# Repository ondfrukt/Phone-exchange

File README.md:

# Phone Exchange - (Under development) # 

## Thanks to! ##

First of all, I want to thank my partner Amanda, who has been som patiant whit me - spending countless hours and weekends by my computer while I, for example, trying to figure out a way to capture pulses from rotary phones, or comforting during mental breakdowns when I was sodering without realizing I was using to low temperatur. If you are reading this - which you might not, since you're probebly so tierd of this project - I just want to say that i love you, and do that even more for standing out with me and my stupid phones.

I would also like to thank two GitHub members from whom I’ve drawn a lot of inspiration.

1. [GadgetReboot](https://github.com/GadgetReboot) with his YouTube videos and repositories about the KS0835F SLIC module and the MT8816 switch matrix, really made this project possible.

3. [Ktownsen](https://github.com/ktownsend-personal/) and his repository [RetroPhone](https://github.com/ktownsend-personal/RetroPhone) showed me that there is someone else out there who thinks an old wired phone network would be cool, and who shares the same passion for making vintage phones work just like they did back in the day. My call process modes and flows are heavily inspired by his work.

## Goal whit the project ##
The project aims to create a local wired phone network that supports both old rotary phones and newer DTMF tone-dialing phones. No intelligence or electronics will be built into the phones themselves; all logic and switching will be handled by the exchange unit. The network will follow a star topology, with two wires leading to each phone.

The goal is for the network to behave just like it did back in the day. Features such as ringing behavior, tones, and call logic will be implemented.

This is a learning project and my personal introduction to programming, Arduino, HTML, and electronics. It might eventually result in nothing more than a pile of electronic scrap and hundreds of non-functional lines of code—but it will definitely provide me with valuable knowledge and a steep learning curve.

### Typical behaviour for all call ###

A typical procedure of the system will be as shown below.
- A hook is lifted, the status of the line changes from "idle" to "ready" and a continuous tone can be heard in the phone hook.
- A phone number is dialed using pulse dialing or DTMF tones, and the digits are captured by the microcontroller.
- Ring pulses are generated to the dialed line and once the hook is picked up, the audio lines are connected between the two lines and the conversation can begin.
- Ones one of the connected phones puts it's handset into the crank, the audio connection between the lines breaks and the call ends.

## Hardware ##

| Component   | Description |
|-------------|-------------|
| ESP32-S3<br>  | - I have always appreciated the ESP family of microcontrollers. After first experimenting with Arduino modules such as the Arduino Uno and Arduino Uno WiFi, it quickly became clear that the ESP32 offered significantly more features at a lower cost. <br> - This module includes 8 MB of flash memory — an important improvement, since the 4 MB version ran out of space during earlier POC work. <br> - Like most ESP chips, it also provides both WiFi and Bluetooth, which are used here for the webserver and WiFi provisioning. The ESP32-C6 was initially considered due to its support for Matter and Zigbee. However, at the time it was not supported in PlatformIO, so the more common ESP32-S3 was selected for this project.
| MT8816<br>               | The MT8816 is a crosspoint swich matrix where you can connect one phone lines audio out to a certain lines audio in, and of course also in the opposite direction so a full audio connection is established more about how it works can be found [here](KiCad/ELEKTRONIK.md) (section 6)       | 
| MT8870<br>            | This circuit translates all tones from DTMF phones into digits.     |
| MCP23017            | GPIO expanders because the ESP32 do not have enough GPIO ports to control all devices                  |
| AD9833 module         | The AD9833 module, which I have three of in the exchange Is sending out tones into the swich matrix and then thuther to lines.               |
| KS0835F<br>          | This module may be the most important one on the breadboard. It handles the phone's behavior and converts it into signals that my ESP can process. It detects whether the phone's hook is on or off and can generate a ring frequency, which would otherwise be very complicated to produce.     |
| PCM5102<br>     | Audio files stored on the ESP are sent to this digital-to-analog converter to output audio messages to the lines when needed. The converter uses I²S communication with the ESP and outputs an analog representation of short, pre-stored audio clips. |
| TMUX4051<br>     | This audio multiplexer acts like a large switch, allowing the audio-out channel of each line to be selectively connected to the MT8870 DTMF detector. Only one channel at a time is connected to the DTMF decoder, and the system continuously sweeps through all lines that are in a state where tone detection is required.

In this way, it is possible to determine which line a tone originates from while using only a single DTMF detector.  |

## Webserver ##
I thought it would be good to have an interface where you could manage the phone system in some way, such as assigning a phone number to a specific line, activating/deactivating lines, changing the ring tone length, and adding some more features. During operation, access to the serial monitor will be limited, so having a way to easily tweak settings and access some debugging information would be useful.

The webserver can be reached at http://phoneexchange.local/ after the provisioning is completed

## MQTT ##
Having an MQTT function is also a goal so that the server can potentially interact with a smart home system such as Home Assistant, opening up the possibility to control home functions — just for fun!

## Line Statuses ##

To handle the logics in the exchange system, all lines has a current status whish triggers different logics in the system when they are changed.

### Status table ###
- Hook  :telephone_receiver: - If the phone hook is on or off due to the status
- Timer :stopwatch: - If the new status initiate a timer
- Audio :loud_sound: -  If a audio is played to the line due to the status (might not be implemented)
- Tone :postal_horn: - if a tone is played to the line due to the status

| Phone status  | Function                              | Hook     | Timer | Audio | Tone |
| ------------- | ------------------------------------- | -------- | ----- |-------|------| 
| idle          | Line is not in use                    | ✅ ON    | ❌    | ➖    | ❌   |
| ready         | Line is ready, waiting for inputs     | ⚪ OFF   | ✅    | ➖    | ✅   |
| puls_dialing  | Rotary dialing in progress            | ⚪ OFF   | ✅    | ➖    | ❌   |
| tone_dialing  | Touch-tone dialing in progress        | ⚪ OFF   | ✅    | ➖    | ❌   |
| busy          | Receiving busy signal                 | ⚪ OFF   | ✅    | ➖    | ✅   |
| fail          | Line failed to connect                | ⚪ OFF   | ✅    | ➖    | ✅   |
| ringing       | Line is ringing (outgoing call)       | ⚪ OFF   | ✅    | ➖    | ✅   |
| connected     | Call is active                        | ⚪ OFF   | ❌    | ➖    | ❌   |
| disconnected  | Call has ended, but line not yet idle | ⚪ OFF   | ✅    | ➖    | ❌   |
| timeout       | Line timed out                        | ⚪ OFF   | ✅    | ➖    | ✅   |
| abandoned     | Line was abandoned                    | ⚪ OFF   | ✅    | ➖    | ✅   |
| incoming      | Incoming call                         | ✅ ON    | ❌    | ➖    | ❌   |
| operator      | Connected to operator                 | ➖       | ❌    | ➖    | ❌   |

### Status flow chart ###
The flowchart below shows how the statuses change based on the behavior of the phone hooks or when status timers expire. This part is largely inspired by [GadgetReboot](https://github.com/GadgetReboot)
 and his repository “Retro Phone”. Many thanks to him!

## Challenges ##

- **SHK interference during ring signal generation**

The KS0835F SLIC's ring voltage (RM HIGH, FR toggling at 20 Hz) induces false SHK transitions, making it impossible to distinguish interference from a real pick-up. Simply ignoring SHK events during ringing suppresses the noise but also swallows genuine pick-ups — the interrupt is consumed and no new one fires during the pause, so the call never connects.

**Workaround in `SHKService`:** SHK events during `RingToggling` are still suppressed. When a line transitions from `RingToggling` to `RingPause`, the SHK pin is immediately force-polled. The debounce filter then confirms the true state: a real pick-up keeps SHK HIGH and the call connects; interference has already cleared and no change is registered. Maximum detection delay equals one ring-burst length (default 1 s).

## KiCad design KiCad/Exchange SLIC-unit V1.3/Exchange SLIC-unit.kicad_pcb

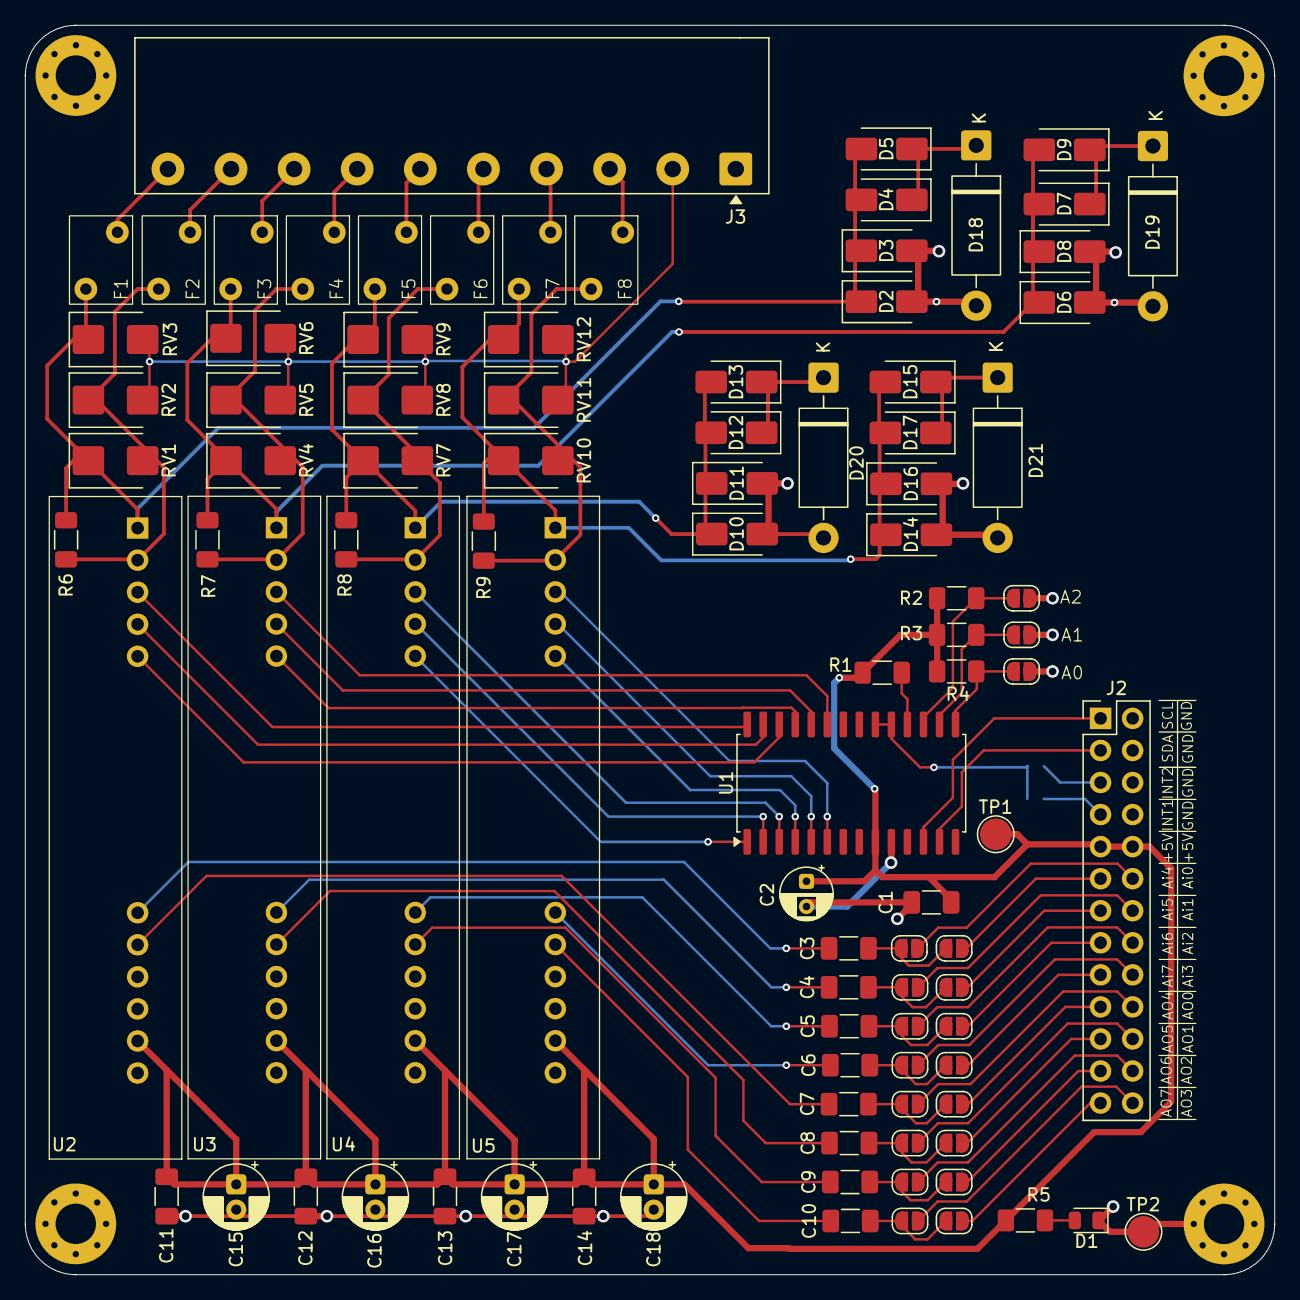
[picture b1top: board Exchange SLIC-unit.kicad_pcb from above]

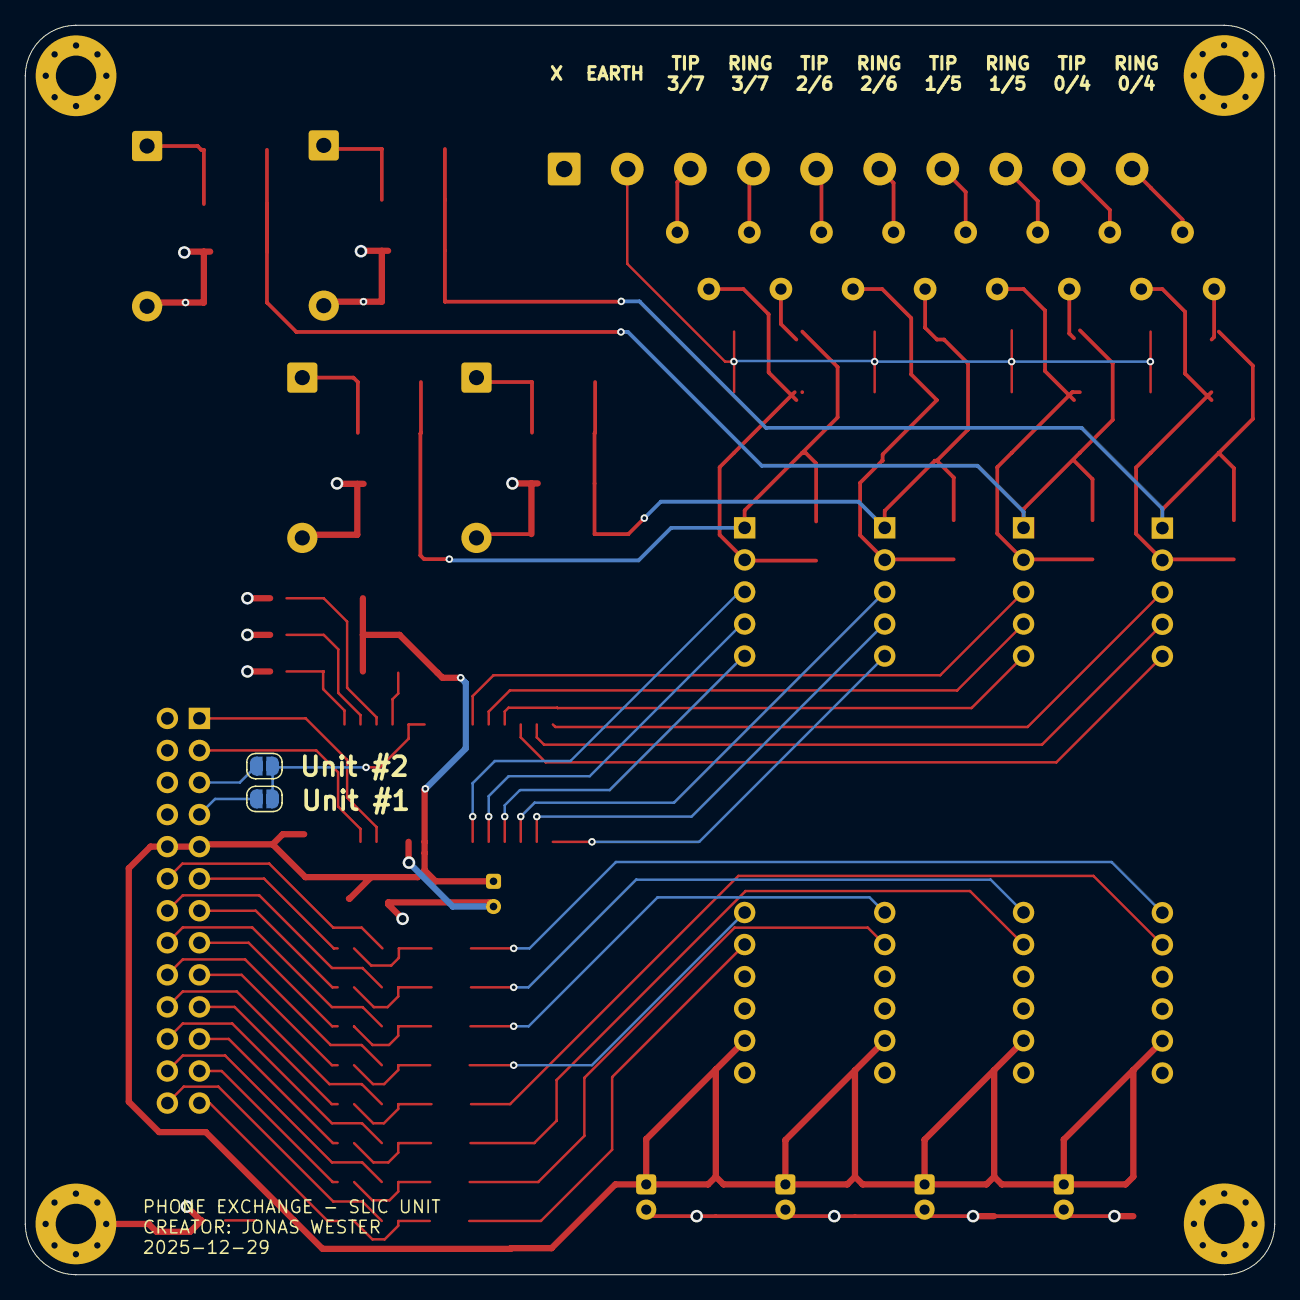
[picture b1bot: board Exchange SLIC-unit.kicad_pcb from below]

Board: 4 copper layers, 99.0 x 99.0 mm, 102 parts (2 on the bottom side), 77 nets.

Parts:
C1, C3, C4, C5, C6, C7, C8, C9, C10, C11, C12, C13, C14: 0.1uF; C_1206_3216Metric_Pad1.33x1.80mm_HandSolder
C2: 10uF; CP_Radial_D4.0mm_P2.00mm
C15, C16, C17, C18: 10uF; CP_Radial_D5.0mm_P2.00mm
D1: POWER LED; LED_0805_2012Metric
D2, D3, D4, D5, D6, D7, D8, D9, D10, D11, D12, D13, D14, D15, D16, D17: SM4004; D_SMA
D18, D19, D20, D21: P6KE51A; D_DO-15_P12.70mm_Horizontal
F1, F2, F3, F4, F5, F6, F7, F8: MF-R025; Fuse_Polyfuse_BK250_5.08mm_P0.8D1.8
H1, H2, H3, H4: MountingHole_Pad; MountingHole_3.2mm_M3_Pad_Via
J2: Conn_02x13_Odd_Even; PinHeader_2x13_P2.54mm_Vertical
J3: Screw_Terminal_01x10; TerminalBlock_Phoenix_MKDS-1,5-10_1x10_P5.00mm_Horizontal -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
JP1, JP2, JP3, JP4, JP5, JP6, JP7, JP8, JP9, JP10, JP11, JP12, JP13, JP14, JP15, JP16, JP17, JP18, JP19, JP20, JP21: SolderJumper_2_Open; SolderJumper-2_P1.3mm_Open_RoundedPad1.0x1.5mm
R1, R2, R3, R4: 10k; R_1206_3216Metric_Pad1.30x1.75mm_HandSolder
R5: 1k; R_1206_3216Metric_Pad1.30x1.75mm_HandSolder
R6, R7, R8, R9: 1M; R_1206_3216Metric_Pad1.30x1.75mm_HandSolder
RV1, RV2, RV3, RV4, RV5, RV6, RV7, RV8, RV9, RV10, RV11, RV12: Varistor; D_SMB
TP1, TP2: TestPoint; TestPoint_Pad_D2.5mm
U1: MCP23017; SOIC-28W_7.5x17.9mm_P1.27mm
U2, U3, U4, U5: KS0835F

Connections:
+5V: C1.2, C2.1, C11.1, C12.1, C13.1, C14.1, C15.1, C16.1, C17.1, C18.1, J2.9, J2.10, R1.1, R2.1, R3.1, R4.1, R5.1, TP1.1, U1.9 (VDD), U2.10 (+VDC), U3.10 (+VDC), U4.10 (+VDC), U5.10 (+VDC)
/Ain_0/4: C3.2, JP1.1 (A), JP9.2 (B)
/Ain_1/5: C4.2, JP2.1 (A), JP10.2 (B)
/Ain_2/6: C5.2, JP3.1 (A), JP11.2 (B)
/Ain_3/7: C6.2, JP4.1 (A), JP12.2 (B)
/Aout_0/4: C7.2, JP5.1 (A), JP13.2 (B)
/Aout_1/5: C8.2, JP6.1 (A), JP14.2 (B)
/Aout_2/6: C9.2, JP7.1 (A), JP15.2 (B)
/Aout_3/7: C10.2, JP8.1 (A), JP16.2 (B)
/FR_0/4: U1.28 (GPA7), U2.3 (F/R)
/FR_1/5: U1.23 (GPA2), U3.3 (F/R)
/FR_2/6: U1.3 (GPB2), U4.3 (F/R)
/FR_3/7: U1.6 (GPB5), U5.3 (F/R)
/MCP_SLIC_INT_1/2: JP17.1 (A), JP18.1 (A), U1.19 (INTB), U1.20 (INTA)
/RING_0/4: F1.2, J3.10
/RING_1/5: F3.2, J3.8
/RING_2/6: F5.2, J3.6
/RING_3/7: F7.2, J3.4
/RM_0/4: U1.27 (GPA6), U2.4 (RM)
/RM_1/5: U1.24 (GPA3), U3.4 (RM)
/RM_2/6: U1.2 (GPB1), U4.4 (RM)
/RM_3/7: U1.5 (GPB4), U5.4 (RM)
/SCL: J2.1, U1.12 (SCL)
/SDA: J2.3, U1.13 (SDA)
/SHK_0/4: U1.26 (GPA5), U2.5 (SHK)
/SHK_1/5: U1.25 (GPA4), U3.5 (SHK)
/SHK_2/6: U1.1 (GPB0), U4.5 (SHK)
/SHK_3/7: U1.4 (GPB3), U5.5 (SHK)
/TIP_0/4: F2.2, J3.9
/TIP_1/5: F4.2, J3.7
/TIP_2/6: F6.2, J3.5
/TIP_3/7: F8.2, J3.3
GND: C1.1, C2.2, C11.2, C12.2, C13.2, C14.2, C15.2, C16.2, C17.2, C18.2, D1.1 (K), D2.2 (A), D3.2 (A), D6.2 (A), D8.2 (A), D10.2 (A), D11.2 (A), D14.2 (A), D16.2 (A), D18.2, D19.2, D20.2, D21.2, H1.1, H2.1, H3.1, H4.1, J2.2, J2.4, J2.6, J2.8, JP19.2 (B), JP20.1 (A), JP21.1 (A), TP2.1, U1.10 (VSS), U2.9 (GND), U3.9 (GND), U4.9 (GND), U5.9 (GND)
GNDPWR: J3.2, RV2.2, RV3.2, RV5.2, RV6.2, RV8.2, RV9.2, RV11.2, RV12.2
unnamed: D1.2 (A), R5.2
unnamed: D2.1 (K), D3.1 (K), D4.2 (A), D5.2 (A), F1.1, R6.1, RV1.1, RV3.1, U2.1 (RING)
unnamed: D4.1 (K), D5.1 (K), D18.1
unnamed: D6.1 (K), D7.2 (A), D8.1 (K), D9.2 (A), F3.1, R7.1, RV4.1, RV6.1, U3.1 (RING)
unnamed: D7.1 (K), D9.1 (K), D19.1
unnamed: D10.1 (K), D11.1 (K), D12.2 (A), D13.2 (A), F5.1, R8.1, RV7.1, RV9.1, U4.1 (RING)
unnamed: D12.1 (K), D13.1 (K), D20.1
unnamed: D14.1 (K), D15.2 (A), D16.1 (K), D17.2 (A), F7.1, R9.1, RV10.1, RV12.1, U5.1 (RING)
unnamed: D15.1 (K), D17.1 (K), D21.1
unnamed: J2.5, JP18.2 (B)
unnamed: J2.7, JP17.2 (B)
unnamed: J2.11, JP9.1 (A)
unnamed: J2.12, JP1.2 (B)
unnamed: J2.13, JP10.1 (A)
unnamed: J2.14, JP2.2 (B)
unnamed: J2.15, JP11.1 (A)
unnamed: J2.16, JP3.2 (B)
unnamed: J2.17, JP12.1 (A)
unnamed: J2.18, JP4.2 (B)
unnamed: J2.19, JP13.1 (A)
unnamed: J2.20, JP5.2 (B)
unnamed: J2.21, JP14.1 (A)
unnamed: J2.22, JP6.2 (B)
unnamed: J2.23, JP15.1 (A)
unnamed: J2.24, JP7.2 (B)
unnamed: J2.25, JP16.1 (A)
unnamed: J2.26, JP8.2 (B)
unnamed: JP19.1 (A), R2.2, U1.17 (A2)
unnamed: JP20.2 (B), R3.2, U1.16 (A1)
unnamed: JP21.2 (B), R4.2, U1.15 (A0)
unnamed: R1.2, U1.18 (~RESET)
unnamed: C3.1, U2.6 (Audio_in)
unnamed: C7.1, U2.7 (Audio_out)
unnamed: F2.1, R6.2, RV1.2, RV2.1, U2.2 (TIP)
unnamed: C4.1, U3.6 (Audio_in)
unnamed: C8.1, U3.7 (Audio_out)
unnamed: F4.1, R7.2, RV4.2, RV5.1, U3.2 (TIP)
unnamed: C5.1, U4.6 (Audio_in)
unnamed: C9.1, U4.7 (Audio_out)
unnamed: F6.1, R8.2, RV7.2, RV8.1, U4.2 (TIP)
unnamed: C6.1, U5.6 (Audio_in)
unnamed: C10.1, U5.7 (Audio_out)
unnamed: F8.1, R9.2, RV10.2, RV11.1, U5.2 (TIP)

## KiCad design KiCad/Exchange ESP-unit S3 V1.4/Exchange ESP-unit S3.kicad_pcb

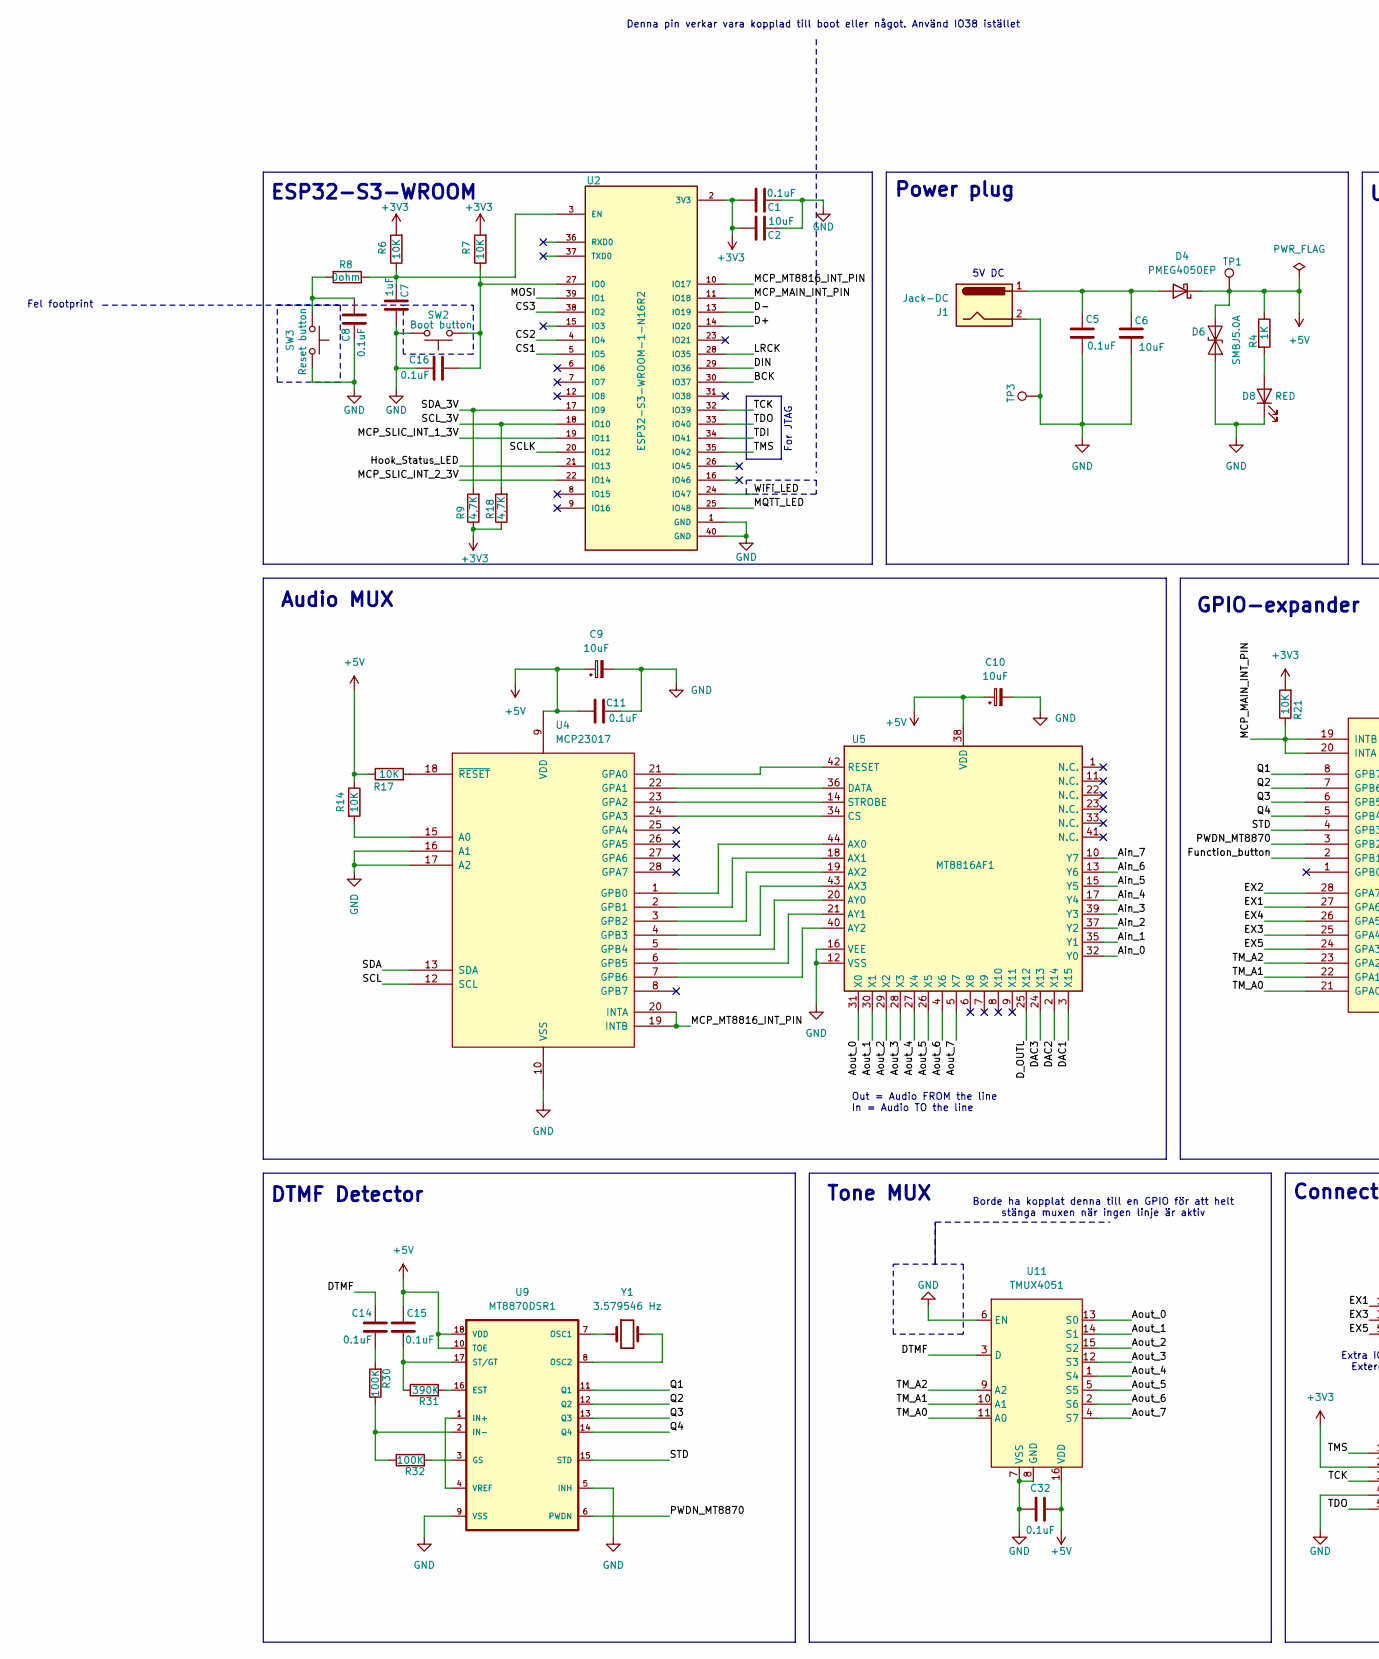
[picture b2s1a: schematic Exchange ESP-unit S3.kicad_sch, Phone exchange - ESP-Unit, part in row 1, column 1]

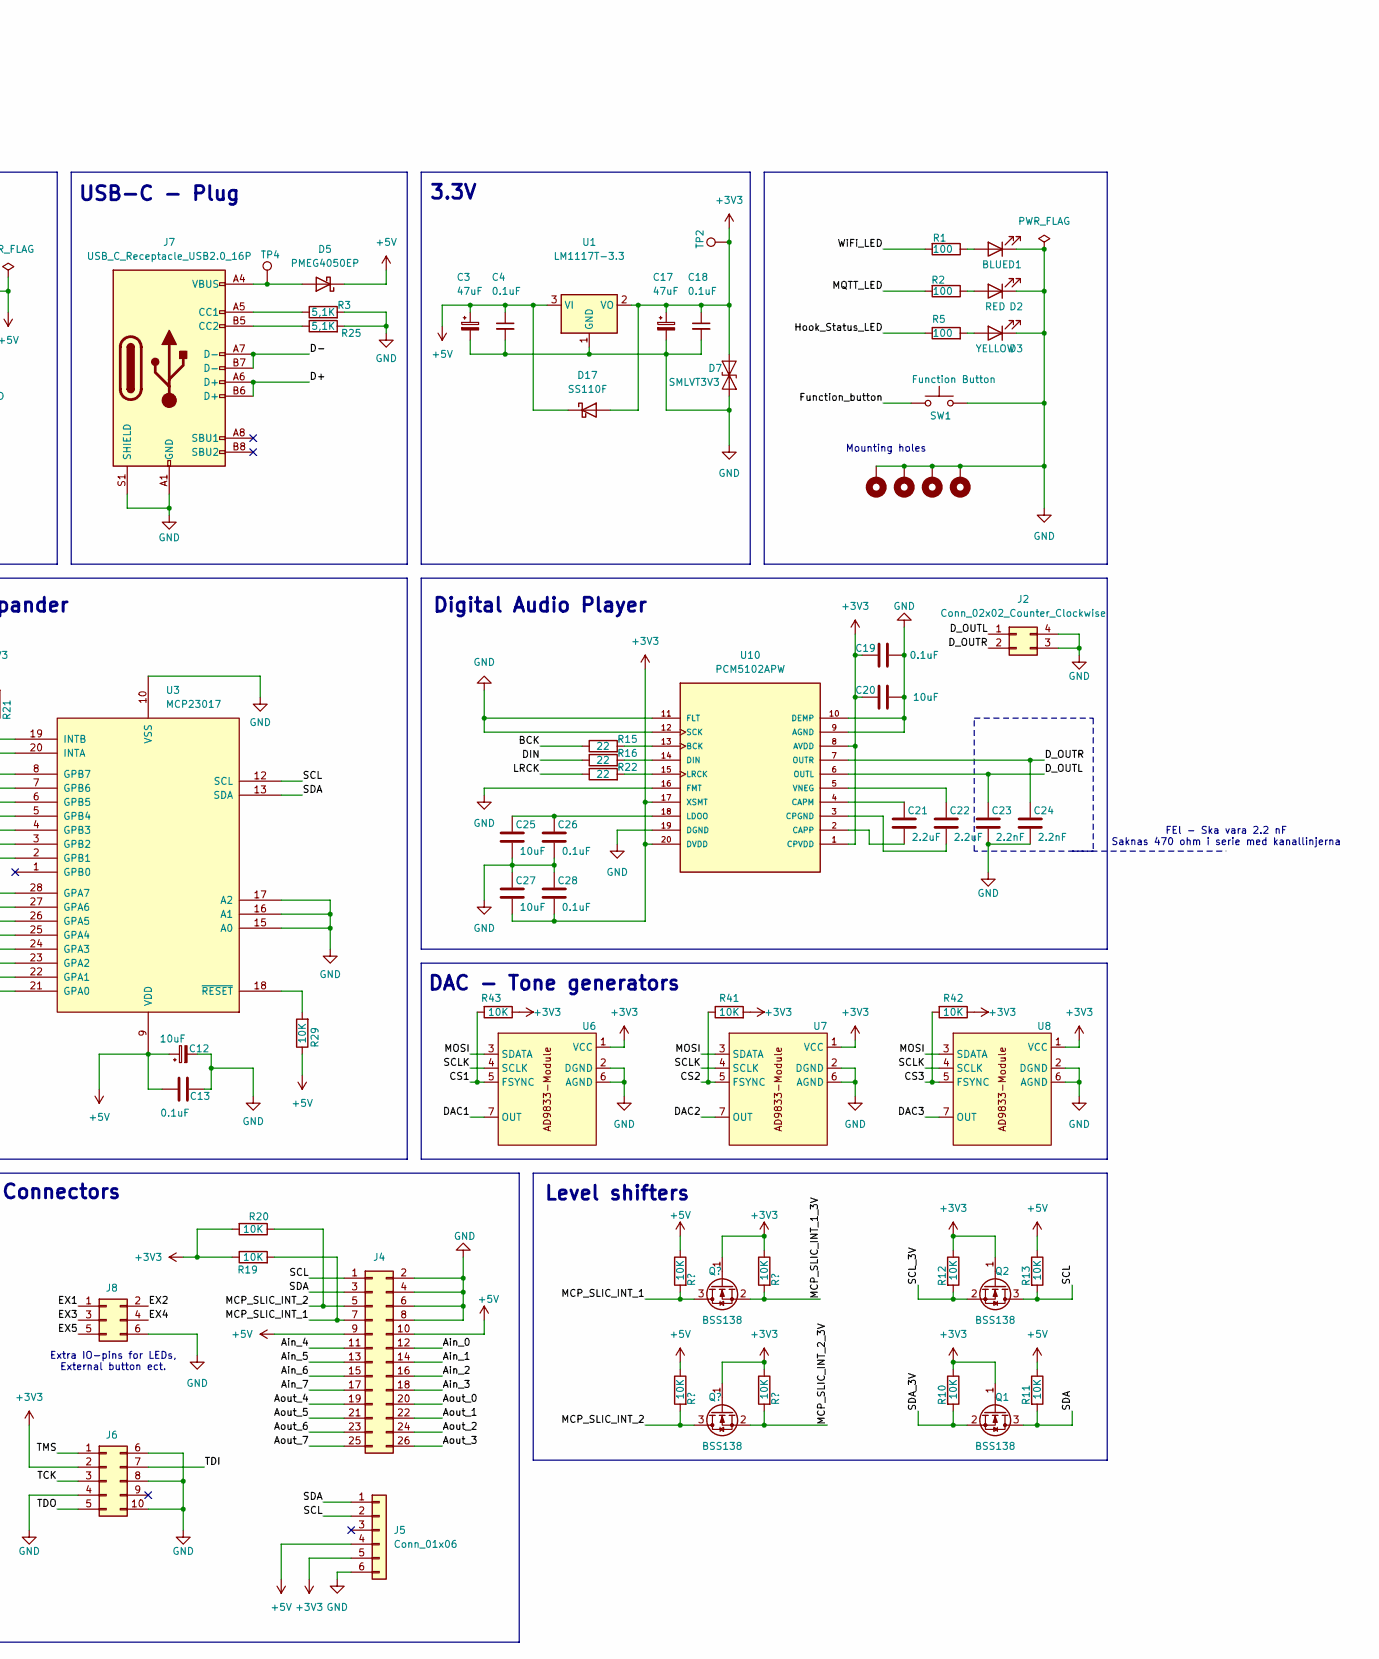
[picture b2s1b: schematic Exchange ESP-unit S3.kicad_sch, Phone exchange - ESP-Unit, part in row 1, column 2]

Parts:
C1, C4, C5, C8, C11, C13, C14, C15, C16, C18, C19, C26, C28, C32: 0.1uF; C_1206_3216Metric_Pad1.33x1.80mm_HandSolder
C2, C6, C20, C25, C27: 10uF; C_1206_3216Metric_Pad1.33x1.80mm_HandSolder
C3, C17: 47uF; CP_Radial_D4.0mm_P2.00mm
C7: 1uF; C_1206_3216Metric_Pad1.33x1.80mm_HandSolder
C9, C10, C12: 10uF; CP_Radial_D4.0mm_P2.00mm
C21, C22: 2.2uF; C_1206_3216Metric_Pad1.33x1.80mm_HandSolder
C23, C24: 2.2nF; C_1206_3216Metric_Pad1.33x1.80mm_HandSolder
D1: BLUE; LED_0805_2012Metric_Pad1.15x1.40mm_HandSolder
D2, D8: RED; LED_0805_2012Metric_Pad1.15x1.40mm_HandSolder
D3: YELLOW; LED_0805_2012Metric_Pad1.15x1.40mm_HandSolder
D4, D5: PMEG4050EP; D_SOD-128
D6: SMBJ5.0A; D_SMB
D7: SMLVT3V3; D_SMB_Handsoldering
D17: SS110F; D_SMA_Handsoldering
H1, H2, H3, H4: MountingHole_Pad; MountingHole_3.2mm_M3_Pad_Via
J1: Jack-DC; BarrelJack_Horizontal
J2: Conn_02x02_Counter_Clockwise; PinHeader_2x02_P2.54mm_Vertical
J4: Conn_02x13_Odd_Even; PinSocket_2x13_P2.54mm_Vertical
J5: Conn_01x06; PinHeader_1x06_P2.54mm_Vertical
J6: Conn_02x05_Top_Bottom; PinSocket_2x05_P2.54mm_Vertical
J7: USB_C_Receptacle_USB2.0_16P; USB_C_Receptacle_GCT_USB4105-xx-A_16P_TopMnt_Horizontal
J8: Conn_02x03_Odd_Even; PinHeader_2x03_P2.54mm_Vertical
Q1, Q2: BSS138; SOT-23
R1, R2, R5: 100; R_1206_3216Metric_Pad1.30x1.75mm_HandSolder
R3, R25: 5,1K; R_1206_3216Metric_Pad1.30x1.75mm_HandSolder
R4: 1K; R_1206_3216Metric_Pad1.30x1.75mm_HandSolder
R6, R7, R10, R11, R12, R13, R14, R17, R19, R20, R21, R29, R41, R42, R43: 10K; R_1206_3216Metric_Pad1.30x1.75mm_HandSolder
R8: 0ohm; R_1206_3216Metric_Pad1.30x1.75mm_HandSolder
R9, R18: 4,7K; R_1206_3216Metric_Pad1.30x1.75mm_HandSolder
R15, R16, R22: 22; R_1206_3216Metric_Pad1.30x1.75mm_HandSolder
R30, R32: 100K; R_1206_3216Metric_Pad1.30x1.75mm_HandSolder
R31: 390K; R_1206_3216Metric_Pad1.30x1.75mm_HandSolder
SW1: Function Button; SW_SPST_TL3305B
SW2: Boot button; SW_SPST_TL3305B
SW3: Reset button; SW_SPST_TL3305B
TP1, TP2, TP3, TP4: TestPoint; TestPoint_Pad_D2.0mm
U1: LM1117T-3.3; TO-220-3_Vertical
U2: ESP32-S3-WROOM-1-N16R2; XCVR_ESP32-S3-WROOM-1-N16; PARTREV v1.0
U3, U4: MCP23017; SOIC-28W_7.5x17.9mm_P1.27mm
U5: MT8816AF1; TQFP-44_10x10mm_P0.8mm
U6, U7, U8: AD9833-module; AD9833-Module
U9: MT8870DSR1; SOIC-18W_7.5x11.6mm_P1.27mm
U10: PCM5102APW; TSSOP-20_4.4x6.5mm_P0.65mm; PARTREV C
U11: TMUX4051; TSSOP-16_4.4x5mm_P0.65mm
Y1: 3.579546 Hz; Crystal_HC49-4H_Vertical

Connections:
+5V: C3.1, C4.1, C9.1, C10.1, C11.1, C12.1, C13.2, C15.1, C32.2, D4.1 (K), D5.1 (K), D6.1 (A1), D17.1 (K), J4.9, J4.10, J5.4, R4.1, R11.1, R13.1, R14.1, R17.1, R29.1, TP1.1, U1.3 (VI), U3.9 (VDD), U4.9 (VDD), U5.38 (VDD), U9.10 (TOE), U9.18 (VDD), U11.16 (VDD)
/Ain_0: J4.12, U5.32 (Y0)
/Ain_1: J4.14, U5.35 (Y1)
/Ain_2: J4.16, U5.37 (Y2)
/Ain_3: J4.18, U5.39 (Y3)
/Ain_4: J4.11, U5.17 (Y4)
/Ain_5: J4.13, U5.15 (Y5)
/Ain_6: J4.15, U5.13 (Y6)
/Ain_7: J4.17, U5.10 (Y7)
/Aout_0: J4.20, U5.31 (X0), U11.13 (S0)
/Aout_1: J4.22, U5.30 (X1), U11.14 (S1)
/Aout_2: J4.24, U5.29 (X2), U11.15 (S2)
/Aout_3: J4.26, U5.28 (X3), U11.12 (S3)
/Aout_4: J4.19, U5.27 (X4), U11.1 (S4)
/Aout_5: J4.21, U5.26 (X5), U11.5 (S5)
/Aout_6: J4.23, U5.4 (X6), U11.2 (S6)
/Aout_7: J4.25, U5.5 (X7), U11.4 (S7)
/BCK: R15.1, U2.30 (IO37)
/CS1: R43.2, U2.5 (IO5), U6.5 (FSYNC)
/CS2: R41.1, U2.4 (IO4), U7.5 (FSYNC)
/CS3: R42.2, U2.38 (IO2), U8.5 (FSYNC)
/D+: J7.A6 (D+), J7.B6 (D+), U2.14 (IO20)
/D-: J7.A7 (D-), J7.B7 (D-), U2.13 (IO19)
/DAC1: U5.3 (X15), U6.7 (OUT)
/DAC2: U5.2 (X14), U7.7 (OUT)
/DAC3: U5.24 (X13), U8.7 (OUT)
/DIN: R16.1, U2.29 (IO36)
/DTMF: C14.2, U11.3 (D)
/D_OUTL: C23.1, J2.1, U5.25 (X12), U10.6 (OUTL)
/D_OUTR: C24.1, J2.2, U10.7 (OUTR)
/EX1: J8.1, U3.27 (GPA6)
/EX2: J8.2, U3.28 (GPA7)
/EX3: J8.3, U3.25 (GPA4)
/EX4: J8.4, U3.26 (GPA5)
/EX5: J8.5, U3.24 (GPA3)
/Function_button: SW1.2, U3.2 (GPB1)
/Hook_Status_LED: R5.1, U2.21 (IO13)
/LRCK: R22.1, U2.28 (IO35)
/MCP_MAIN_INT_PIN: R21.1, U2.11 (IO18), U3.19 (INTB), U3.20 (INTA)
/MCP_MT8816_INT_PIN: U2.10 (IO17), U4.19 (INTB), U4.20 (INTA)
/MOSI: U2.39 (IO1), U6.3 (SDATA), U7.3 (SDATA), U8.3 (SDATA)
/MQTT_LED: R2.2, U2.25 (IO48)
/PWDN_MT8870: U3.3 (GPB2), U9.6 (PWDN)
/Q1: U3.8 (GPB7), U9.11 (Q1)
/Q2: U3.7 (GPB6), U9.12 (Q2)
/Q3: U3.6 (GPB5), U9.13 (Q3)
/Q4: U3.5 (GPB4), U9.14 (Q4)
/SCL: J4.1, J5.2, Q2.3 (D), R13.2, U3.12 (SCL), U4.12 (SCL)
/SCLK: U2.20 (IO12), U6.4 (SCLK), U7.4 (SCLK), U8.4 (SCLK)
/SCL_3V: Q2.2 (S), R12.2, R18.2, U2.18 (IO10)
/SDA: J4.3, J5.1, Q1.3 (D), R11.2, U3.13 (SDA), U4.13 (SDA)
/SDA_3V: Q1.2 (S), R9.2, R10.2, U2.17 (IO9)
/STD: U3.4 (GPB3), U9.15 (STD)
/TCK: J6.3, U2.32 (IO39)
/TDI: J6.7, U2.34 (IO41)
/TDO: J6.5, U2.33 (IO40)
/TMS: J6.1, U2.35 (IO42)
/TM_A0: U3.21 (GPA0), U11.11 (A0)
/TM_A1: U3.22 (GPA1), U11.10 (A1)
/TM_A2: U3.23 (GPA2), U11.9 (A2)
/WiFi_LED: R1.2, U2.24 (IO47)
GND: C1.1, C2.1, C3.2, C4.2, C5.2, C6.2, C7.2, C8.1, C9.2, C10.2, C11.2, C12.2, C13.1, C16.1, C17.2, C18.2, C19.2, C20.2, C23.2, C24.2, C25.2, C26.2, C27.1, C28.1, C32.1, D1.1 (K), D2.1 (K), D3.1 (K), D6.2 (A2), D7.2 (A2), D8.1 (K), H1.1, H2.1, H3.1, H4.1, J1.2, J2.3, J2.4, J4.2, J4.4, J4.6, J4.8, J5.6, J6.4, J6.6, J6.8, J6.10, J7.A1 (GND), J7.A12 (GND), J7.B1 (GND), J7.B12 (GND), J7.S1 (SHIELD), J8.6, R3.2, R25.2, SW1.1, SW2.2, SW3.2, TP3.1, U1.1 (GND), U2.1 (GND), U2.40 (GND), U3.10 (VSS), U3.15 (A0), U3.16 (A1), U3.17 (A2), U4.10 (VSS), U4.16 (A1), U4.17 (A2), U5.12 (VSS), U5.16 (VEE), U6.2 (DGND), U6.6 (AGND), U7.2 (DGND), U7.6 (AGND), U8.2 (DGND), U8.6 (AGND), U9.5 (INH), U9.9 (VSS), U10.9 (AGND), U10.10 (DEMP), U10.11 (FLT), U10.12 (SCK), U10.16 (FMT), U10.19 (DGND), U11.6 (EN), U11.7 (VSS), U11.8 (GND)
unnamed: C8.2, R8.2, SW3.1
unnamed: C14.1, R30.2
unnamed: D1.2 (A), R1.1
unnamed: D2.2 (A), R2.1
unnamed: D3.2 (A), R5.2
unnamed: C5.1, C6.1, D4.2 (A), J1.1
unnamed: D5.2 (A), J7.A4 (VBUS), J7.A9 (VBUS), J7.B4 (VBUS), J7.B9 (VBUS), TP4.1
unnamed: D8.2 (A), R4.2
unnamed: J7.A5 (CC1), R3.1
unnamed: J7.B5 (CC2), R25.1
unnamed: C7.1, R6.1, R8.1, U2.3 (EN)
unnamed: C16.2, R7.1, SW2.1, U2.27 (IO0)
unnamed: R29.2, U3.18 (~RESET)
unnamed: R14.2, U4.15 (A0)
unnamed: U4.21 (GPA0), U5.42 (RESET)
unnamed: U4.22 (GPA1), U5.36 (DATA)
unnamed: U4.23 (GPA2), U5.14 (STROBE)
unnamed: U4.24 (GPA3), U5.34 (CS)
unnamed: U4.1 (GPB0), U5.44 (AX0)
unnamed: U4.2 (GPB1), U5.18 (AX1)
unnamed: U4.3 (GPB2), U5.19 (AX2)
unnamed: U4.4 (GPB3), U5.43 (AX3)
unnamed: U4.5 (GPB4), U5.20 (AY0)
unnamed: U4.6 (GPB5), U5.21 (AY1)
unnamed: U4.7 (GPB6), U5.40 (AY2)
unnamed: R17.2, U4.18 (~RESET)
unnamed: R31.2, U9.16 (EST)
unnamed: R32.2, U9.3 (GS)
unnamed: U9.1 (IN+), U9.4 (VREF)
unnamed: R30.1, R32.1, U9.2 (IN-)
unnamed: U9.7 (OSC1), Y1.1
unnamed: U9.8 (OSC2), Y1.2
unnamed: C15.2, R31.1, U9.17 (ST/GT)
unnamed: R15.2, U10.13 (BCK)
unnamed: C21.1, U10.4 (CAPM)
unnamed: C21.2, U10.2 (CAPP)
unnamed: C22.2, U10.3 (CPGND)
unnamed: R16.2, U10.14 (DIN)
unnamed: C25.1, C26.1, U10.18 (LDOO)
unnamed: R22.2, U10.15 (LRCK)
unnamed: C22.1, U10.5 (VNEG)

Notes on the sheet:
Audio MUX
Fel footprint
ESP32-S3-WROOM
GPIO-expander
DTMF Detector
3.3V
DAC - Tone generators
Extra IO-pins for LEDs, External button ect.
Digital Audio Player
Denna pin verkar vara kopplad till boot eller något. Använd IO38 istället
Power plug
Mounting holes
Tone MUX
For JTAG
Connectors
FEl - Ska vara 2.2 nF Saknas 470 ohm i serie med kanallinjerna
USB-C - Plug
5V DC
Out = Audio FROM the line In = Audio TO the line
Level shifters
Borde ha kopplat denna till en GPIO för att helt stänga muxen när ingen linje är aktiv

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
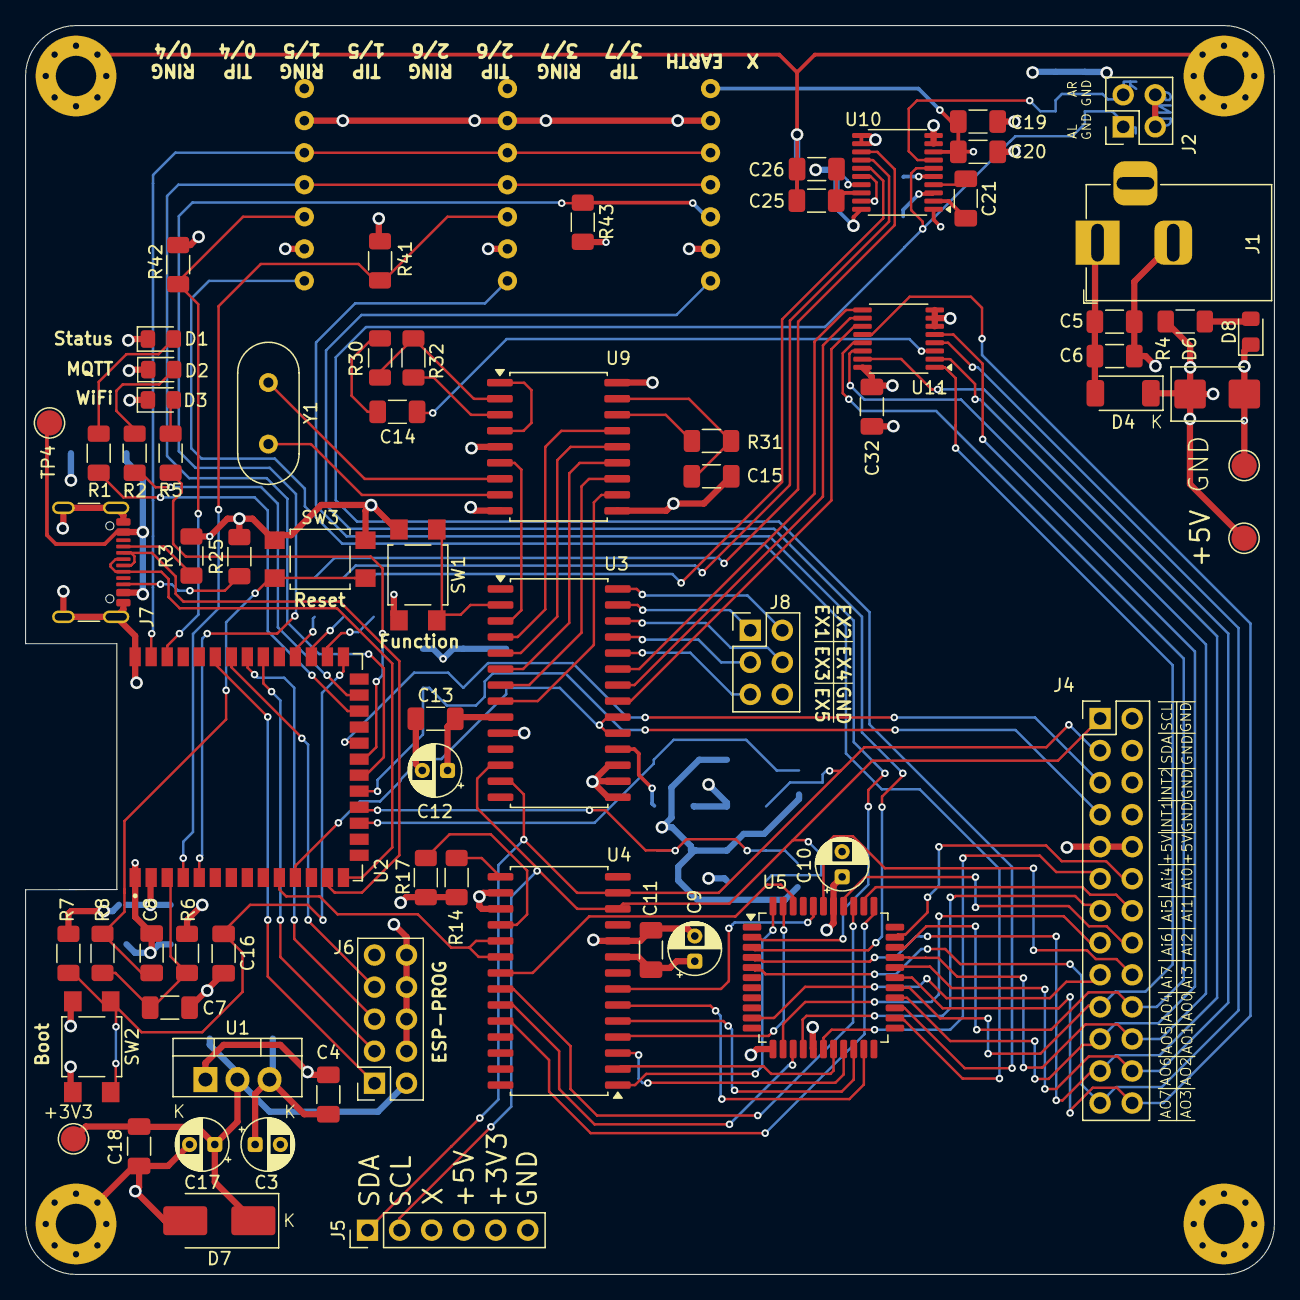
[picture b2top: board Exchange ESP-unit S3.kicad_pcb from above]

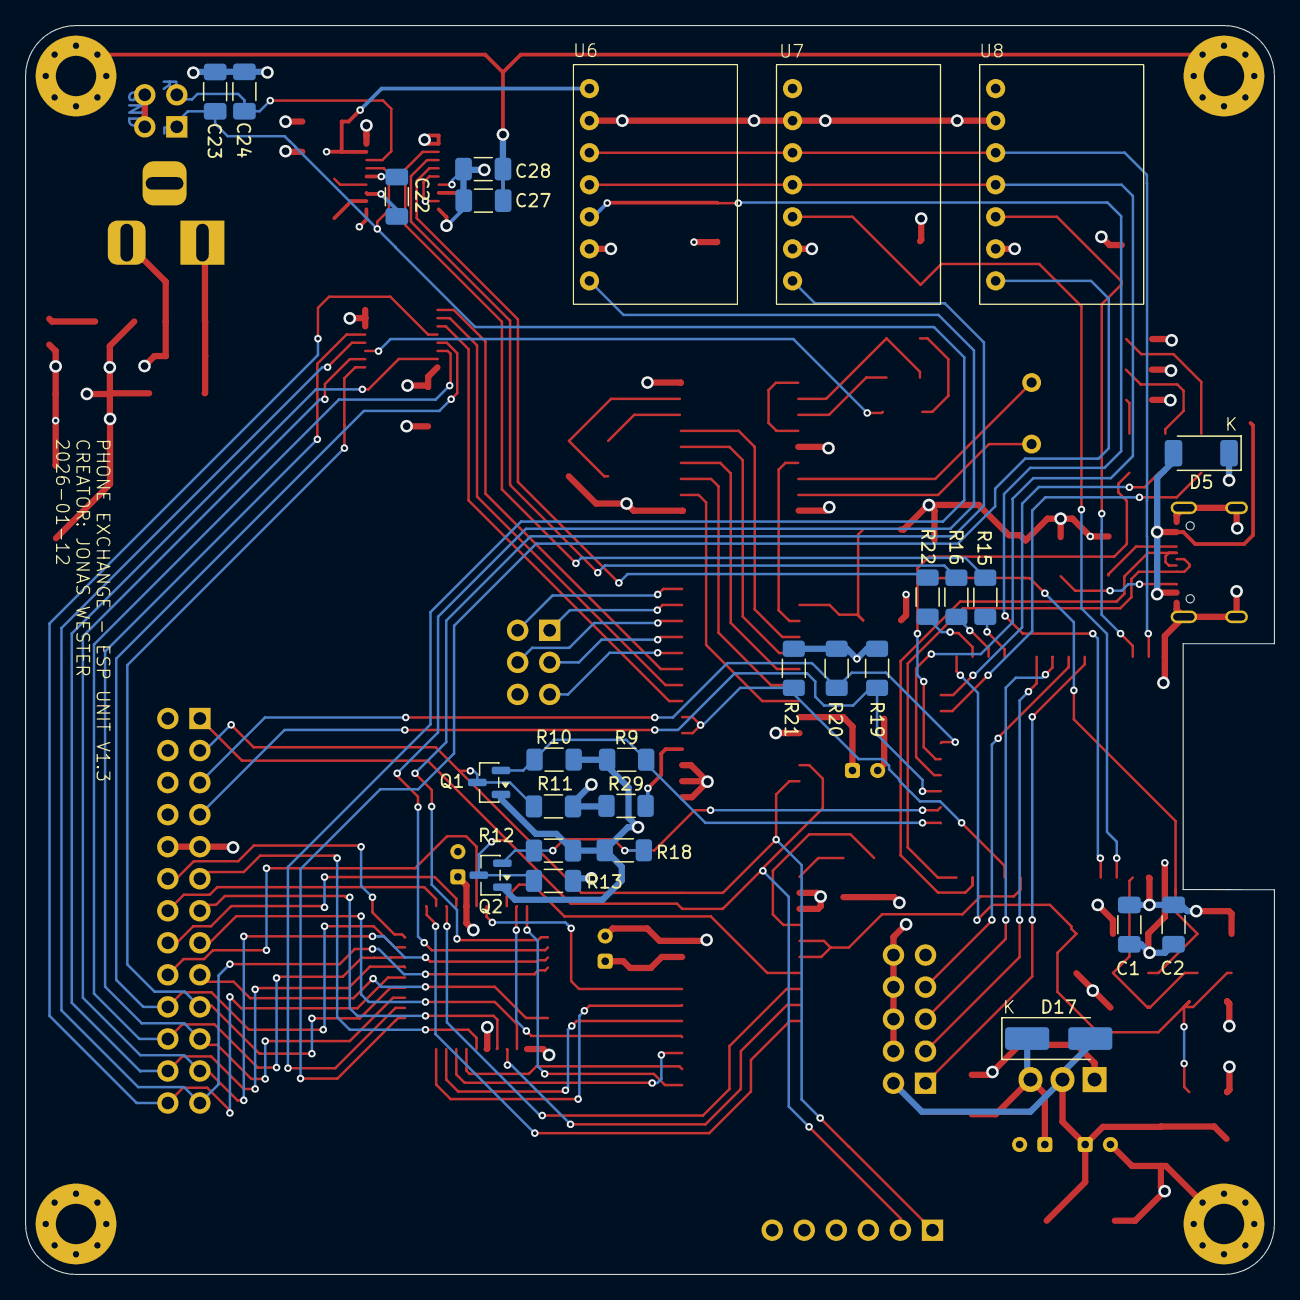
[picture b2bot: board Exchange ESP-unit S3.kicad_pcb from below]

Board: 4 copper layers, 99.0 x 99.0 mm, 100 parts (27 on the bottom side), 106 nets.
